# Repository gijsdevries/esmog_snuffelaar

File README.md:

# esmog_snuffelaar

## Software

## Hardware
### Orders
   - **Order #1** v1.0, 22-6-26, ce8a10

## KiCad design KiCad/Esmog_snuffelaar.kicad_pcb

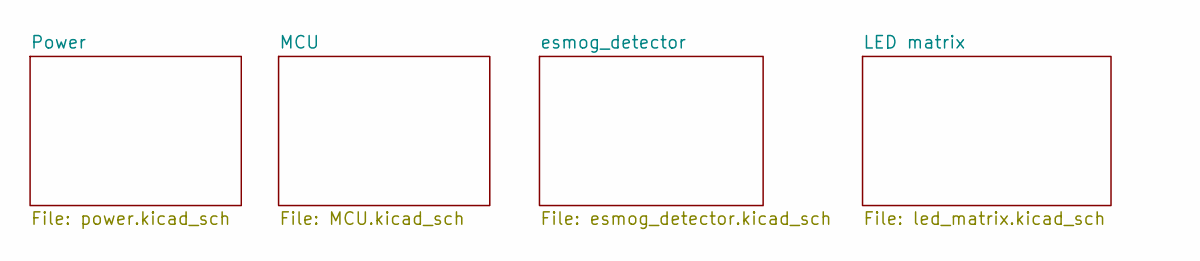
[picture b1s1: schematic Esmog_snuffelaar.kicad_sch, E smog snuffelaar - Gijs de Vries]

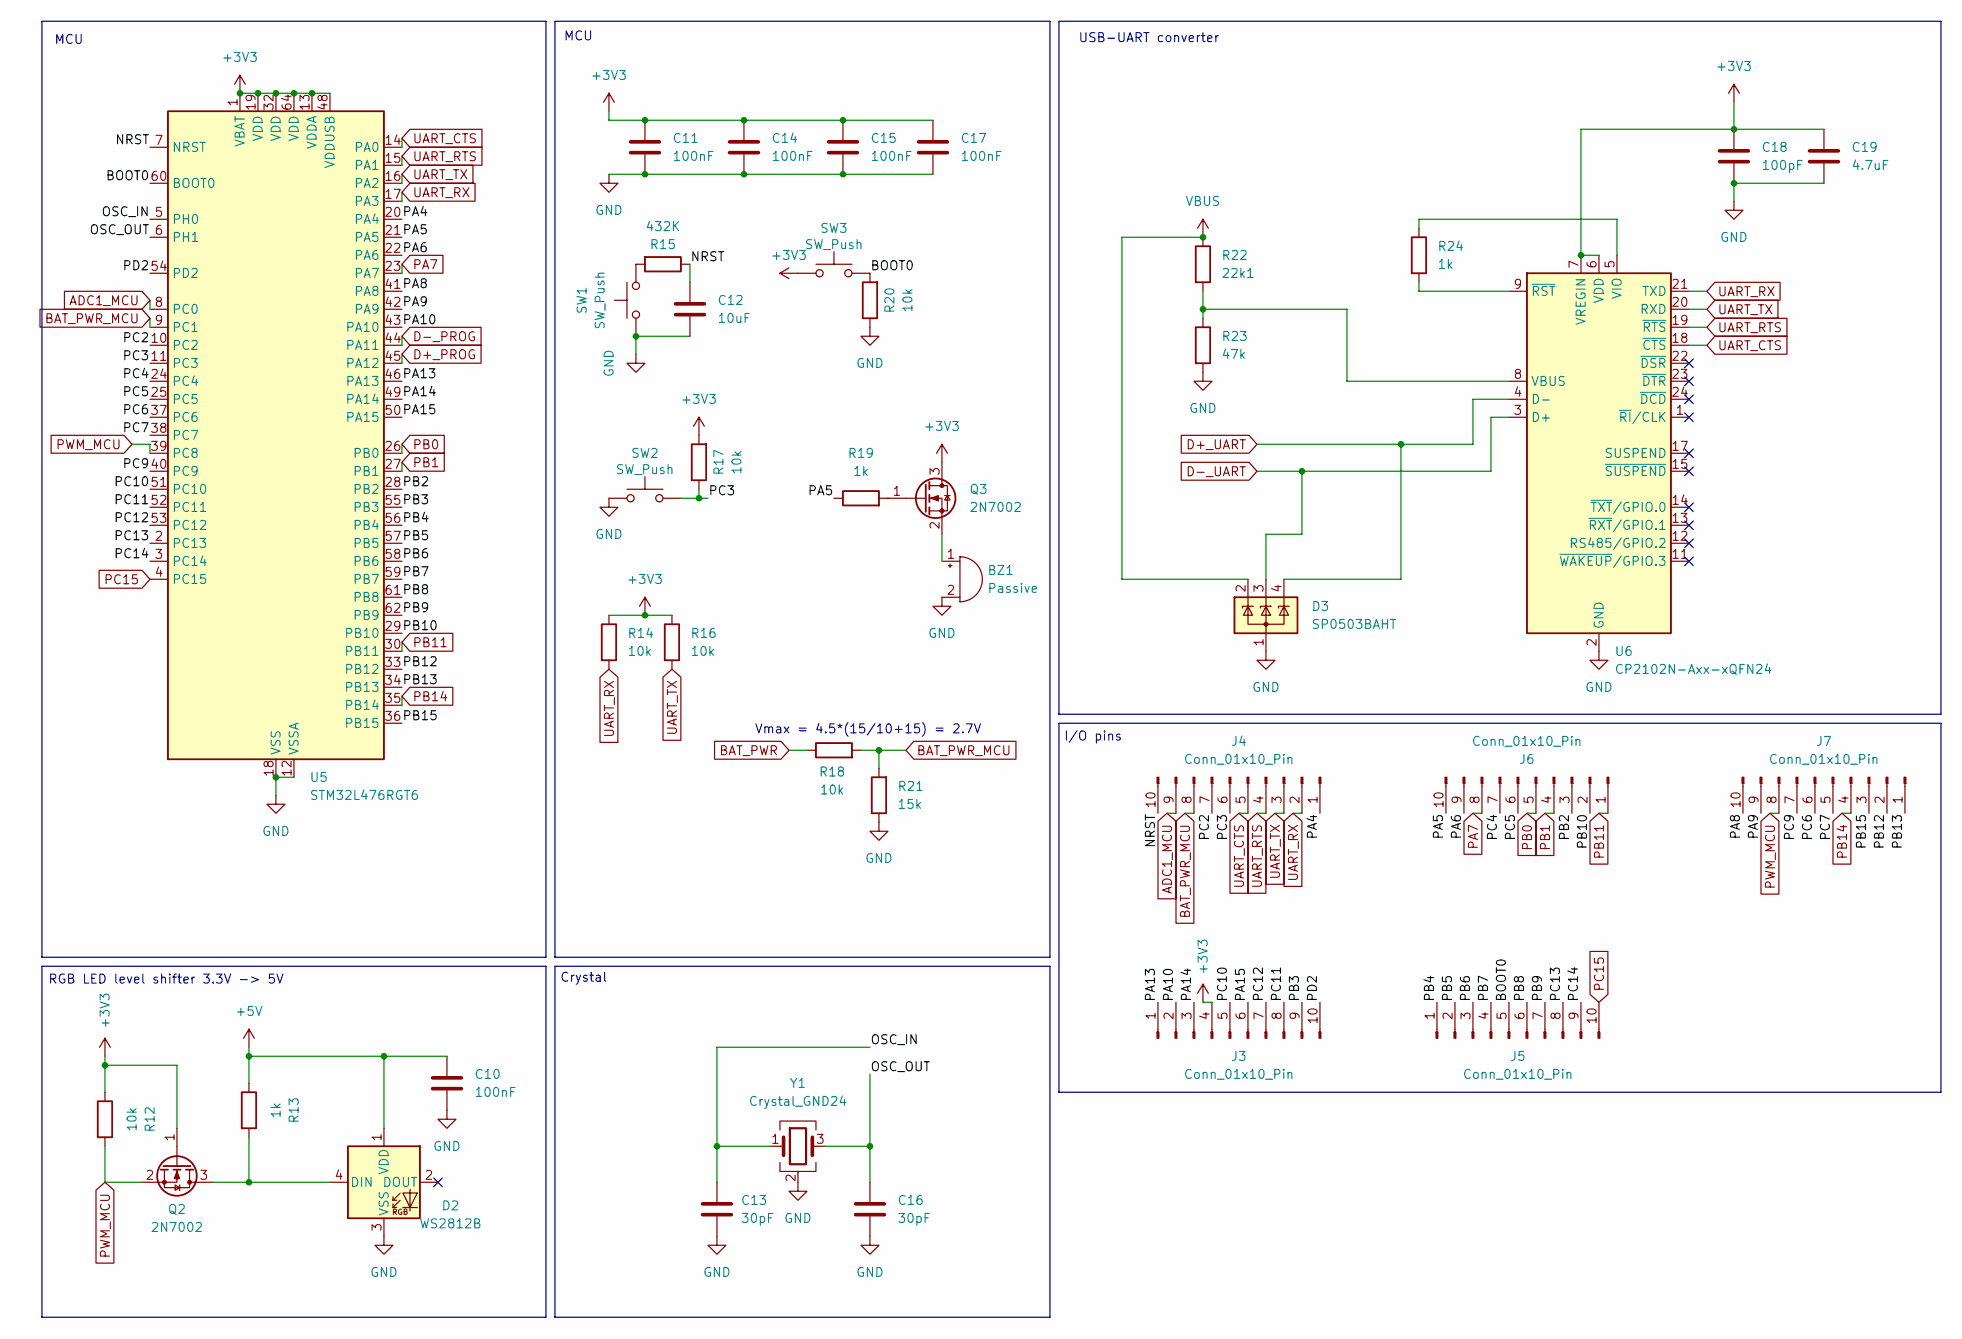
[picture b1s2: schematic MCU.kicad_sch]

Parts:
BZ1: Passive; Buzzer_TDK_PS1240P02BT_D12.2mm_H6.5mm; JLCPCB Part C76871
C10, C11, C14, C15, C17: 100nF; C_0603_1608Metric_Pad1.08x0.95mm_HandSolder; JLCPCB Part C1591
C12: 10uF; C_0603_1608Metric_Pad1.08x0.95mm_HandSolder; JLCPCB Part C1691
C13, C16: 30pF; C_0603_1608Metric_Pad1.08x0.95mm_HandSolder; JLCPCB Part C1658
C18: 100pF; C_0603_1608Metric_Pad1.08x0.95mm_HandSolder; JLCPCB Part C14858
C19: 4.7uF; C_0603_1608Metric_Pad1.08x0.95mm_HandSolder; JLCPCB Part C1705
D2: WS2812B; LED_WS2812B_PLCC4_5.0x5.0mm_P3.2mm; JLCPCB Part C527089
D3: SP0503BAHT; SOT-143; JLCPCB Part C7074
J3, J4, J5, J6, J7: Conn_01x10_Pin; PinHeader_2x05_P2.54mm_Vertical; JLCPCB Part C42431818
Q2, Q3: 2N7002; SOT-23; JLCPCB Part C916396
R12, R14, R16, R17, R18, R20: 10k; R_0603_1608Metric_Pad0.98x0.95mm_HandSolder; JLCPCB Part C2930027
R13, R19, R24: 1k; R_0603_1608Metric_Pad0.98x0.95mm_HandSolder; JLCPCB Part C2907002
R15: 432K; R_0603_1608Metric_Pad0.98x0.95mm_HandSolder; JLCPCB Part C234529
R21: 15k; R_0603_1608Metric_Pad0.98x0.95mm_HandSolder; JLCPCB Part C114682
R22: 22k1; R_0603_1608Metric_Pad0.98x0.95mm_HandSolder; JLCPCB Part C25961
R23: 47k; R_0603_1608Metric_Pad0.98x0.95mm_HandSolder; JLCPCB Part C2907042
SW1, SW2, SW3: SW_Push; SW_Push_SPST_NO_Alps_SKRK; JLCPCB Part C115357
U5: STM32L476RGT6; LQFP-64_10x10mm_P0.5mm; JLCPCB Part C74797
U6: CP2102N-Axx-xQFN24; QFN-24-1EP_4x4mm_P0.5mm_EP2.6x2.6mm; JLCPCB Part C964632
Y1: Crystal_GND24; Crystal_SMD_Abracon_ABM8AIG-4Pin_3.2x2.5mm; JLCPCB Part C9002

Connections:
+3V3: C11.2, C14.2, C15.2, C17.2, C18.1, C19.1, J3.4, Q2.1 (G), Q3.3 (D), R12.1, R14.1, R16.1, R17.2, SW3.1, U5.1 (VBAT), U5.13 (VDDA), U5.19 (VDD), U5.32 (VDD), U5.48 (VDDUSB), U5.64 (VDD), U6.6 (VDD), U6.7 (VREGIN); also elsewhere on the board
+5V: C10.2, D2.1 (VDD), R13.1; also elsewhere on the board
/MCU/BOOT0: J5.5, R20.2, SW3.2, U5.60 (BOOT0)
/MCU/NRST: C12.2, J4.10, R15.1, U5.7 (NRST)
/MCU/OSC_IN: C13.2, U5.5 (PH0), Y1.1
/MCU/OSC_OUT: C16.2, U5.6 (PH1), Y1.3
/MCU/PA4: J4.1, U5.20 (PA4)
/MCU/PA5: J6.10, R19.1, U5.21 (PA5)
/MCU/PA6: J6.9, U5.22 (PA6)
/MCU/PA8: J7.10, U5.41 (PA8)
/MCU/PA9: J7.9, U5.42 (PA9)
/MCU/PA10: J3.2, U5.43 (PA10)
/MCU/PA13: J3.1, U5.46 (PA13)
/MCU/PA14: J3.3, U5.49 (PA14)
/MCU/PA15: J3.6, U5.50 (PA15)
/MCU/PB2: J6.3, U5.28 (PB2)
/MCU/PB3: J3.9, U5.55 (PB3)
/MCU/PB4: J5.1, U5.56 (PB4)
/MCU/PB5: J5.2, U5.57 (PB5)
/MCU/PB6: J5.3, U5.58 (PB6)
/MCU/PB7: J5.4, U5.59 (PB7)
/MCU/PB8: J5.6, U5.61 (PB8)
/MCU/PB9: J5.7, U5.62 (PB9)
/MCU/PB10: J6.2, U5.29 (PB10)
/MCU/PB12: J7.2, U5.33 (PB12)
/MCU/PB13: J7.1, U5.34 (PB13)
/MCU/PB15: J7.3, U5.36 (PB15)
/MCU/PC2: J4.7, U5.10 (PC2)
/MCU/PC3: J4.6, R17.1, SW2.2, U5.11 (PC3)
/MCU/PC4: J6.7, U5.24 (PC4)
/MCU/PC5: J6.6, U5.25 (PC5)
/MCU/PC6: J7.6, U5.37 (PC6)
/MCU/PC7: J7.5, U5.38 (PC7)
/MCU/PC9: J7.7, U5.40 (PC9)
/MCU/PC10: J3.5, U5.51 (PC10)
/MCU/PC11: J3.8, U5.52 (PC11)
/MCU/PC12: J3.7, U5.53 (PC12)
/MCU/PC13: J5.8, U5.2 (PC13)
/MCU/PC14: J5.9, U5.3 (PC14)
/MCU/PD2: J3.10, U5.54 (PD2)
ADC1_MCU: J4.9, U5.8 (PC0); also elsewhere on the board
BAT_PWR: R18.1; also elsewhere on the board
BAT_PWR_MCU: J4.8, R18.2, R21.2, U5.9 (PC1)
D+_PROG: U5.45 (PA12); also elsewhere on the board
D+_UART: D3.4 (K), U6.4 (D-); also elsewhere on the board
D-_PROG: U5.44 (PA11); also elsewhere on the board
D-_UART: D3.3 (K), U6.3 (D+); also elsewhere on the board
GND: BZ1.2 (-), C10.1, C11.1, C12.1, C13.1, C14.1, C15.1, C16.1, C17.1, C18.2, C19.2, D2.3 (VSS), D3.1 (A), R20.1, R21.1, R23.2, SW1.1, SW2.1, U5.12 (VSSA), U5.18 (VSS), U5.31 (VSS), U5.47 (VSS), U5.63 (VSS), U6.2 (GND), U6.25 (GND), Y1.2 (G), Y1.4 (G); also elsewhere on the board
unnamed: BZ1.1 (+), Q3.2 (S)
unnamed: D2.4 (DIN), Q2.3 (D), R13.2
unnamed: Q3.1 (G), R19.2
unnamed: R15.2, SW1.2
unnamed: R22.2, R23.1, U6.8 (VBUS)
unnamed: R24.1, U6.5 (VIO)
unnamed: R24.2, U6.9 (~RST)
PA7: J6.8, U5.23 (PA7); also elsewhere on the board
PB0: J6.5, U5.26 (PB0); also elsewhere on the board
PB1: J6.4, U5.27 (PB1); also elsewhere on the board
PB11: J6.1, U5.30 (PB11); also elsewhere on the board
PB14: J7.4, U5.35 (PB14); also elsewhere on the board
PC15: J5.10, U5.4 (PC15)
PWM_MCU: J7.8, Q2.2 (S), R12.2, U5.39 (PC8)
UART_CTS: J4.5, U5.14 (PA0), U6.18 (~CTS)
UART_RTS: J4.4, U5.15 (PA1), U6.19 (~RTS)
UART_RX: J4.2, R14.2, U5.17 (PA3), U6.21 (TXD)
UART_TX: J4.3, R16.2, U5.16 (PA2), U6.20 (RXD)
VBUS: D3.2 (K), R22.1; also elsewhere on the board

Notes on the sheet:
MCU
I/O pins
Crystal
Vmax = 4.5*(15/10+15) = 2.7V
RGB LED level shifter 3.3V -> 5V
USB-UART converter

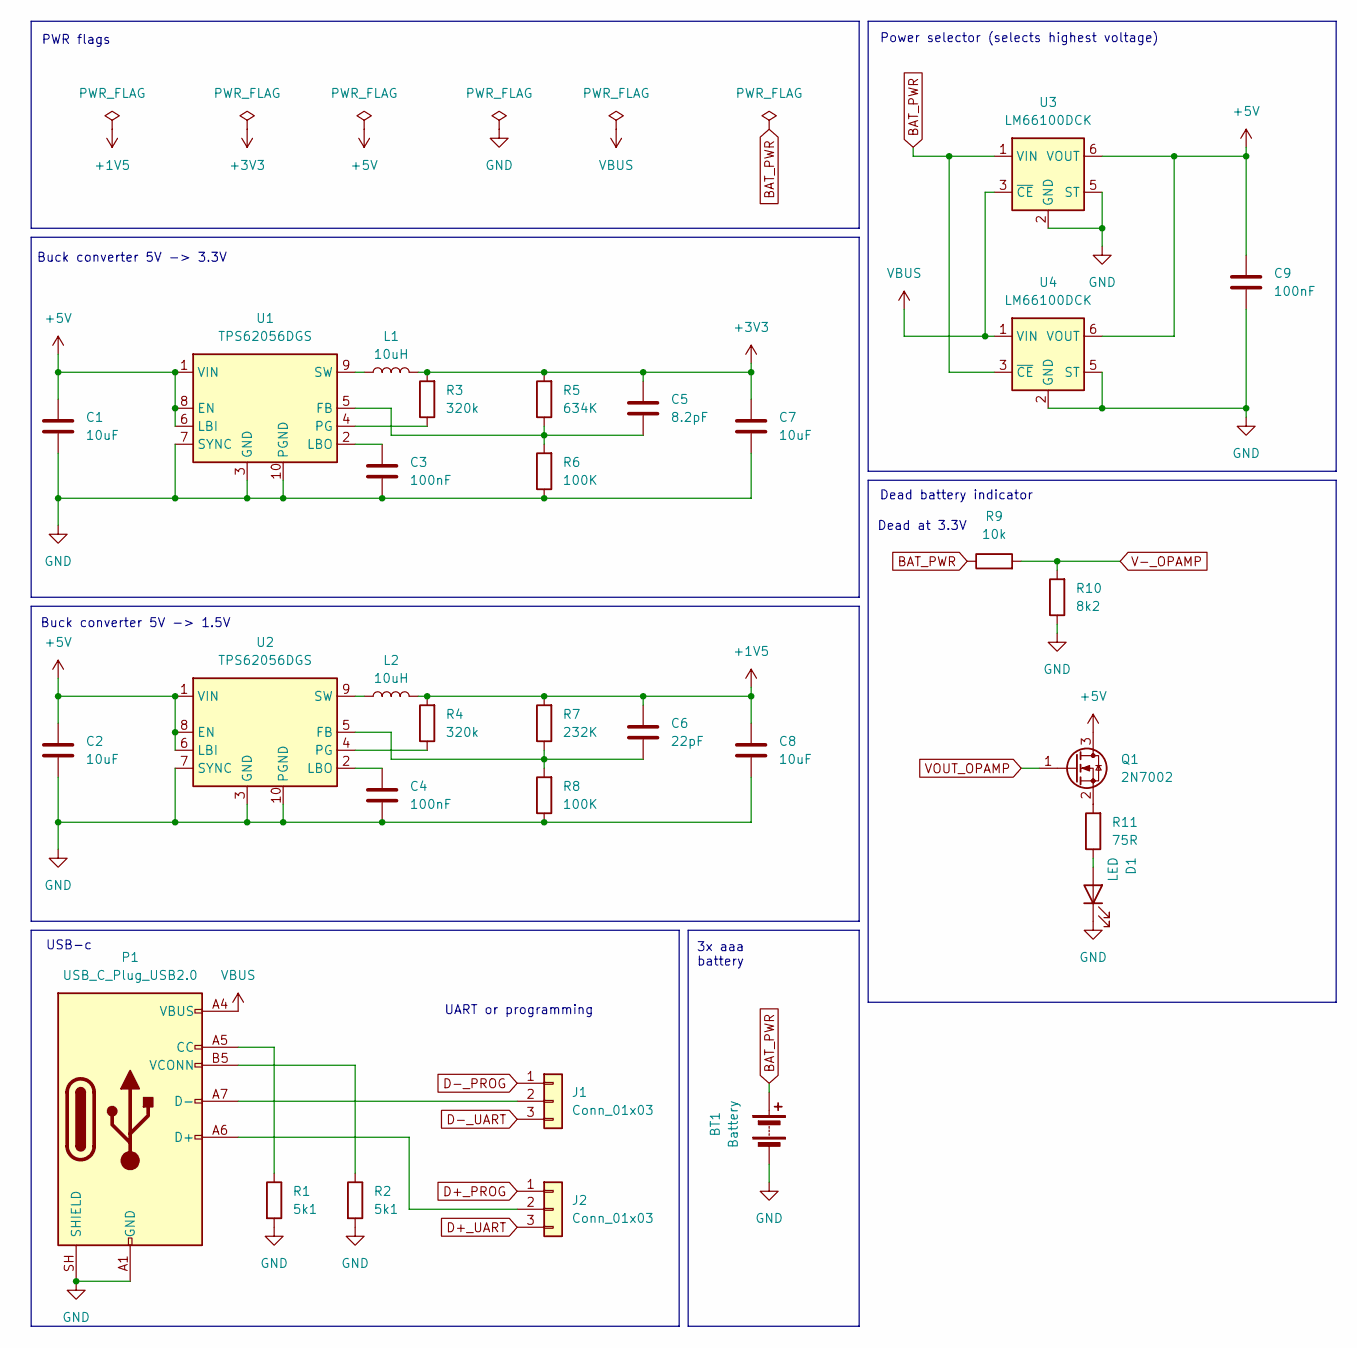
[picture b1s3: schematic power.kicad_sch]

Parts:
BT1: Battery; BatteryHolder_Keystone_2479_3xAAA; JLCPCB Part C5290193
C1, C2, C7, C8: 10uF; C_0603_1608Metric_Pad1.08x0.95mm_HandSolder; JLCPCB Part C1691
C3, C4, C9: 100nF; C_0603_1608Metric_Pad1.08x0.95mm_HandSolder; JLCPCB Part C1591
C5: 8.2pF; C_0603_1608Metric_Pad1.08x0.95mm_HandSolder; JLCPCB Part C1685
C6: 22pF; C_0603_1608Metric_Pad1.08x0.95mm_HandSolder; JLCPCB Part C1653
D1: LED; LED_0603_1608Metric; JLCPCB Part C2286
J1, J2: Conn_01x03; PinHeader_1x03_P2.54mm_Vertical
L1, L2: 10uH; L_APV_APH0420; JLCPCB Part C181721
P1: USB_C_Plug_USB2.0; USB_C_Receptacle_XKB_U262-16XN-4BVC11; JLCPCB Part C3025063
Q1: 2N7002; SOT-23; JLCPCB Part C916396
R1, R2: 5k1; R_0603_1608Metric_Pad0.98x0.95mm_HandSolder; JLCPCB Part C2907044
R3, R4: 320k; R_0603_1608Metric_Pad0.98x0.95mm_HandSolder; JLCPCB Part C862677
R5: 634K; R_0603_1608Metric_Pad0.98x0.95mm_HandSolder; JLCPCB Part C65831
R6, R8: 100K; R_0603_1608Metric_Pad0.98x0.95mm_HandSolder; JLCPCB Part C2906980
R7: 232K; R_0603_1608Metric_Pad0.98x0.95mm_HandSolder; JLCPCB Part C22913
R9: 10k; R_0603_1608Metric_Pad0.98x0.95mm_HandSolder; JLCPCB Part C2930027
R10: 8k2; R_0603_1608Metric_Pad0.98x0.95mm_HandSolder; JLCPCB Part C114637
R11: 75R; R_0603_1608Metric_Pad0.98x0.95mm_HandSolder; JLCPCB Part C112309
U1, U2: TPS62056DGS; TSSOP-10_3x3mm_P0.5mm; JLCPCB Part C7097
U3, U4: LM66100DCK; SOT-363_SC-70-6; JLCPCB Part C2832141

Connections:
+1V5: C6.2, C8.2, L2.2, R4.2, R7.2; also elsewhere on the board
+3V3: C5.2, C7.2, L1.2, R3.2, R5.2; also elsewhere on the board
+5V: C1.2, C2.2, C9.2, Q1.3 (D), U1.1 (VIN), U1.6 (LBI), U1.8 (EN), U2.1 (VIN), U2.6 (LBI), U2.8 (EN), U3.6 (VOUT), U4.6 (VOUT); also elsewhere on the board
BAT_PWR: BT1.1 (+), R9.1, U3.1 (VIN), U4.3 (~CE); also elsewhere on the board
D+_PROG: J2.1; also elsewhere on the board
D+_UART: J2.3; also elsewhere on the board
D-_PROG: J1.1; also elsewhere on the board
D-_UART: J1.3; also elsewhere on the board
GND: BT1.2 (-), C1.1, C2.1, C3.1, C4.1, C7.1, C8.1, C9.1, D1.1 (K), P1.A1 (GND), P1.A12 (GND), P1.B1 (GND), P1.B12 (GND), P1.SH (SHIELD), R1.2, R2.2, R6.1, R8.1, R10.1, U1.3 (GND), U1.7 (SYNC), U1.10 (PGND), U2.3 (GND), U2.7 (SYNC), U2.10 (PGND), U3.2 (GND), U3.5 (ST), U4.2 (GND), U4.5 (ST); also elsewhere on the board
unnamed: D1.2 (A), R11.1
unnamed: J1.2, P1.A7 (D-)
unnamed: J2.2, P1.A6 (D+)
unnamed: P1.A5 (CC), R1.1
unnamed: P1.B5 (VCONN), R2.1
unnamed: Q1.2 (S), R11.2
unnamed: C5.1, R5.1, R6.2, U1.5 (FB)
unnamed: C3.2, U1.2 (LBO)
unnamed: R3.1, U1.4 (PG)
unnamed: L1.1, U1.9 (SW)
unnamed: C6.1, R7.1, R8.2, U2.5 (FB)
unnamed: C4.2, U2.2 (LBO)
unnamed: R4.1, U2.4 (PG)
unnamed: L2.1, U2.9 (SW)
V-_OPAMP: R9.2, R10.2; also elsewhere on the board
VBUS: P1.A4 (VBUS), P1.A9 (VBUS), P1.B4 (VBUS), P1.B9 (VBUS), U3.3 (~CE), U4.1 (VIN); also elsewhere on the board
VOUT_OPAMP: Q1.1 (G); also elsewhere on the board

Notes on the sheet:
3x aaa battery
Buck converter 5V -> 3.3V
Dead at 3.3V
Power selector (selects highest voltage)
Buck converter 5V -> 1.5V
UART or programming
Dead battery indicator
PWR flags
USB-c

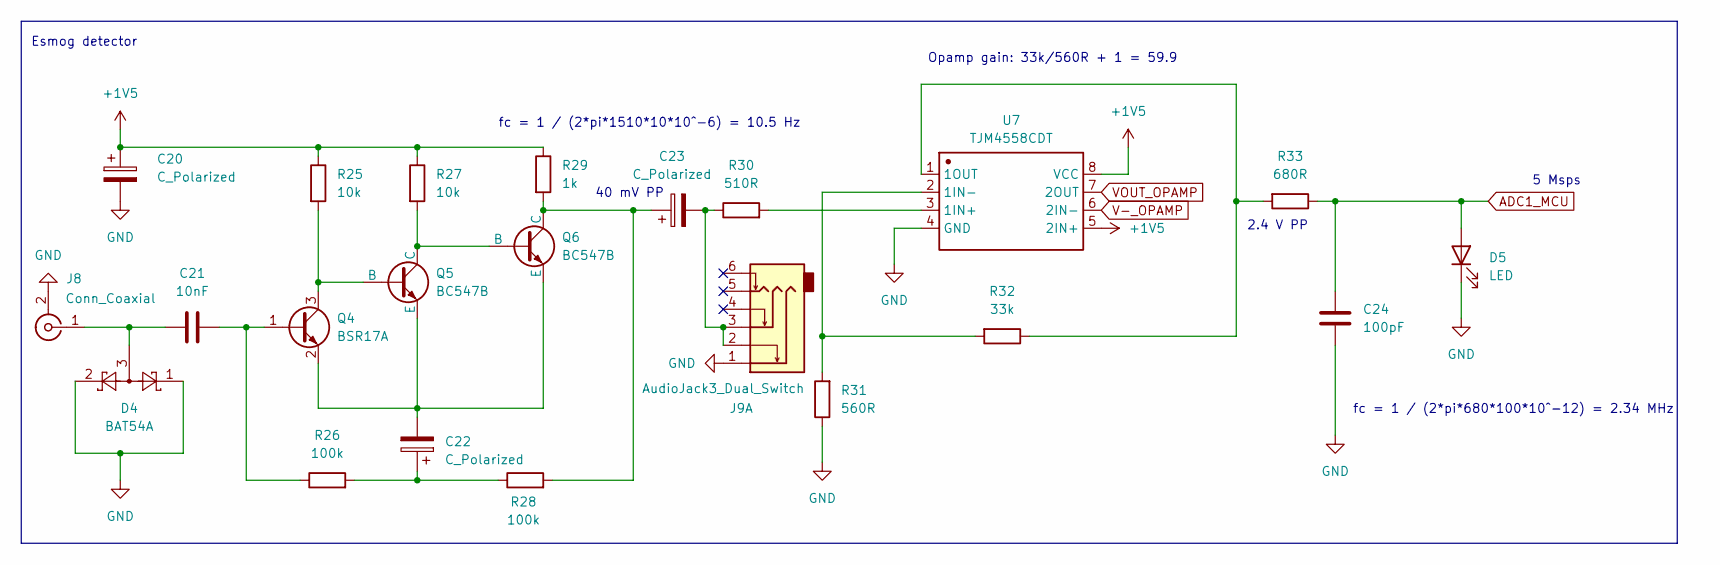
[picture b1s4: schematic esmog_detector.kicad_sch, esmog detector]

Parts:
C20, C22, C23: C_Polarized; CP_Elec_4x5.4; JLCPCB Part C213487
C21: 10nF; C_0603_1608Metric_Pad1.08x0.95mm_HandSolder; JLCPCB Part C1589
C24: 100pF; C_0603_1608Metric_Pad1.08x0.95mm_HandSolder; JLCPCB Part C14858
D4: BAT54A; SOT-23; JLCPCB Part C12743
D5: LED; LED_0603_1608Metric; JLCPCB Part C2286
J8: Conn_Coaxial; CONN-TH_AV-5; JLCPCB Part C18080
J9: AudioJack3_Dual_Switch; Audio_jack; JLCPCB Part C128987
Q4: BSR17A; SOT-23; JLCPCB Part C46682449
Q5, Q6: BC547B; TO-92; JLCPCB Part C713613
R25, R27: 10k; R_0603_1608Metric_Pad0.98x0.95mm_HandSolder; JLCPCB Part C2930027
R26, R28: 100k; R_0603_1608Metric_Pad0.98x0.95mm_HandSolder; JLCPCB Part C2906980
R29: 1k; R_0603_1608Metric_Pad0.98x0.95mm_HandSolder; JLCPCB Part C2907002
R30: 510R; R_0603_1608Metric_Pad0.98x0.95mm_HandSolder; JLCPCB Part C113299
R31: 560R; R_0603_1608Metric_Pad0.98x0.95mm_HandSolder; JLCPCB Part C23204
R32: 33k; R_0603_1608Metric_Pad0.98x0.95mm_HandSolder; JLCPCB Part C844778
R33: 680R; R_0603_1608Metric_Pad0.98x0.95mm_HandSolder; JLCPCB Part C23228
U7: TJM4558CDT; SOIC-8_5.3x5.3mm_P1.27mm; Manufacturer Part TJM4558CDT; JLCPCB Part C6955

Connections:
+1V5: C20.1, R25.1, R27.1, R29.1, U7.5 (2IN+), U7.8 (VCC); also elsewhere on the board
ADC1_MCU: C24.2, D5.2 (A), R33.1; also elsewhere on the board
GND: C20.2, C24.1, D4.1, D4.2, D5.1 (K), J8.2 (Ext), J9.1, R31.1, U7.4 (GND); also elsewhere on the board
unnamed: C22.1, R26.2, R28.1
unnamed: C23.2, J9.2, J9.3, R30.1
unnamed: C21.1, D4.3, J8.1 (In)
unnamed: C21.2, Q4.1 (B), R26.1
unnamed: Q4.3 (C), Q5.2 (B), R25.2
unnamed: C22.2, Q4.2 (E), Q5.3 (E), Q6.3 (E)
unnamed: Q5.1 (C), Q6.2 (B), R27.2
unnamed: C23.1, Q6.1 (C), R28.2, R29.2
unnamed: R30.2, U7.3 (1IN+)
unnamed: R31.2, R32.2, U7.2 (1IN-)
unnamed: R32.1, R33.2, U7.1 (1OUT)
V-_OPAMP: U7.6 (2IN-); also elsewhere on the board
VOUT_OPAMP: U7.7 (2OUT); also elsewhere on the board

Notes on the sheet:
5 Msps
fc = 1 / (2*pi*680*100*10^-12) = 2.34 MHz
40 mV PP
Esmog detector
fc = 1 / (2*pi*1510*10*10^-6) = 10.5 Hz
Opamp gain: 33k/560R + 1 = 59.9
2.4 V PP

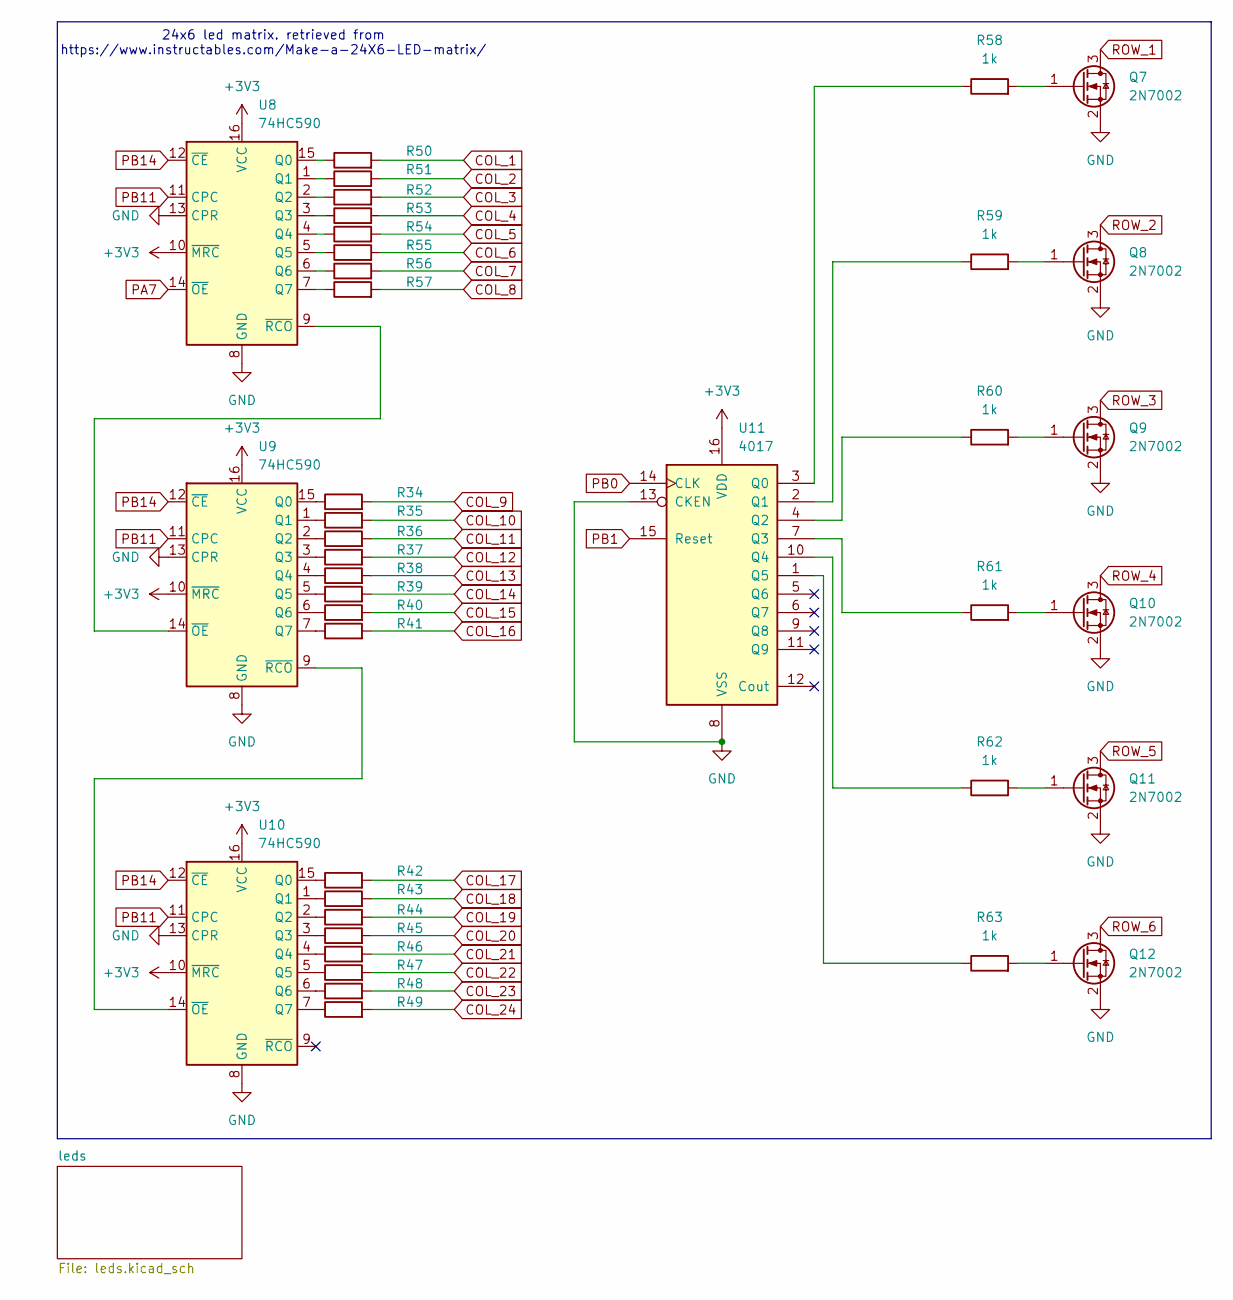
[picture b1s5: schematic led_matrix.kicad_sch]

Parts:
Q7, Q8, Q9, Q10, Q11, Q12: 2N7002; SOT-23; JLCPCB Part C916396
R34, R35, R36, R37, R38, R39, R40, R41, R42, R43, R44, R45, R46, R47, R48, R49, R50, R51, R52, R53, R54, R55, R56, R57: 75R; R_0603_1608Metric_Pad0.98x0.95mm_HandSolder; JLCPCB Part C112309
R58, R59, R60, R61, R62, R63: 1k; R_0603_1608Metric_Pad0.98x0.95mm_HandSolder; JLCPCB Part C2907002
U8, U9, U10: 74HC590; SOIC-16_3.9x9.9mm_P1.27mm; JLCPCB Part C5947
U11: 4017; SO-16_3.9x9.9mm_P1.27mm; JLCPCB Part C11349

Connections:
+3V3: U8.10 (~MRC), U8.16 (VCC), U9.10 (~MRC), U9.16 (VCC), U10.10 (~MRC), U10.16 (VCC), U11.16 (VDD); also elsewhere on the board
COL_1: R50.2; also elsewhere on the board
COL_2: R51.2; also elsewhere on the board
COL_3: R52.2; also elsewhere on the board
COL_4: R53.2; also elsewhere on the board
COL_5: R54.2; also elsewhere on the board
COL_6: R55.2; also elsewhere on the board
COL_7: R56.2; also elsewhere on the board
COL_8: R57.2; also elsewhere on the board
COL_9: R34.2; also elsewhere on the board
COL_10: R35.2; also elsewhere on the board
COL_11: R36.2; also elsewhere on the board
COL_12: R37.2; also elsewhere on the board
COL_13: R38.2; also elsewhere on the board
COL_14: R39.2; also elsewhere on the board
COL_15: R40.2; also elsewhere on the board
COL_16: R41.2; also elsewhere on the board
COL_17: R42.2; also elsewhere on the board
COL_18: R43.2; also elsewhere on the board
COL_19: R44.2; also elsewhere on the board
COL_20: R45.2; also elsewhere on the board
COL_21: R46.2; also elsewhere on the board
COL_22: R47.2; also elsewhere on the board
COL_23: R48.2; also elsewhere on the board
COL_24: R49.2; also elsewhere on the board
GND: Q7.2 (S), Q8.2 (S), Q9.2 (S), Q10.2 (S), Q11.2 (S), Q12.2 (S), U8.8 (GND), U8.13 (CPR), U9.8 (GND), U9.13 (CPR), U10.8 (GND), U10.13 (CPR), U11.8 (VSS), U11.13 (CKEN); also elsewhere on the board
unnamed: Q7.1 (G), R58.2
unnamed: Q8.1 (G), R59.2
unnamed: Q9.1 (G), R60.2
unnamed: Q10.1 (G), R61.2
unnamed: Q11.1 (G), R62.2
unnamed: Q12.1 (G), R63.2
unnamed: R50.1, U8.15 (Q0)
unnamed: R51.1, U8.1 (Q1)
unnamed: R52.1, U8.2 (Q2)
unnamed: R53.1, U8.3 (Q3)
unnamed: R54.1, U8.4 (Q4)
unnamed: R55.1, U8.5 (Q5)
unnamed: R56.1, U8.6 (Q6)
unnamed: R57.1, U8.7 (Q7)
unnamed: U8.9 (~RCO), U9.14 (~OE)
unnamed: R34.1, U9.15 (Q0)
unnamed: R35.1, U9.1 (Q1)
unnamed: R36.1, U9.2 (Q2)
unnamed: R37.1, U9.3 (Q3)
unnamed: R38.1, U9.4 (Q4)
unnamed: R39.1, U9.5 (Q5)
unnamed: R40.1, U9.6 (Q6)
unnamed: R41.1, U9.7 (Q7)
unnamed: R42.1, U10.15 (Q0)
unnamed: R43.1, U10.1 (Q1)
unnamed: R44.1, U10.2 (Q2)
unnamed: R45.1, U10.3 (Q3)
unnamed: R46.1, U10.4 (Q4)
unnamed: R47.1, U10.5 (Q5)
unnamed: R48.1, U10.6 (Q6)
unnamed: R49.1, U10.7 (Q7)
unnamed: U9.9 (~RCO), U10.14 (~OE)
unnamed: R58.1, U11.3 (Q0)
unnamed: R59.1, U11.2 (Q1)
unnamed: R60.1, U11.4 (Q2)
unnamed: R61.1, U11.7 (Q3)
unnamed: R62.1, U11.10 (Q4)
unnamed: R63.1, U11.1 (Q5)
PA7: U8.14 (~OE); also elsewhere on the board
PB0: U11.14 (CLK); also elsewhere on the board
PB1: U11.15 (Reset); also elsewhere on the board
PB11: U8.11 (CPC), U9.11 (CPC), U10.11 (CPC); also elsewhere on the board
PB14: U8.12 (~CE), U9.12 (~CE), U10.12 (~CE); also elsewhere on the board
ROW_1: Q7.3 (D); also elsewhere on the board
ROW_2: Q8.3 (D); also elsewhere on the board
ROW_3: Q9.3 (D); also elsewhere on the board
ROW_4: Q10.3 (D); also elsewhere on the board
ROW_5: Q11.3 (D); also elsewhere on the board
ROW_6: Q12.3 (D); also elsewhere on the board

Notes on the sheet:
24x6 led matrix. retrieved from https://www.instructables.com/Make-a-24X6-LED-matrix/

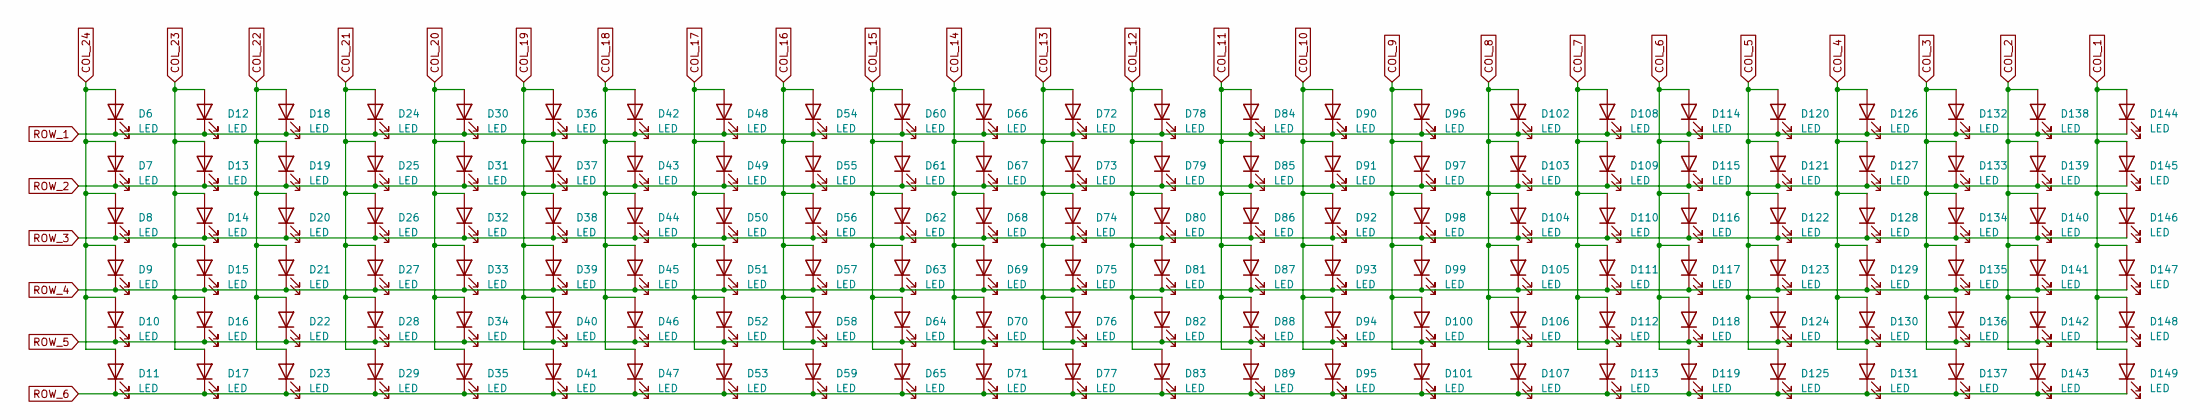
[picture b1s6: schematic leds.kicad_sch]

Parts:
D6, D7, D8, D9, D10, D11, D12, D13, D14, D15, D16, D17, D18, D19, D20, D21, D22, D23, D24, D25, D26, D27, D28, D29, D30, D31, D32, D33, D34, D35, D36, D37, D38, D39, D40, D41, D42, D43, D44, D45, D46, D47, D48, D49, D50, D51, D52, D53, D54, D55, D56, D57, D58, D59, D60, D61, D62, D63, D64, D65, D66, D67, D68, D69, D70, D71, D72, D73, D74, D75, D76, D77, D78, D79, D80, D81, D82, D83, D84, D85, D86, D87, D88, D89, D90, D91, D92, D93, D94, D95, D96, D97, D98, D99, D100, D101, D102, D103, D104, D105, D106, D107, D108, D109, D110, D111, D112, D113, D114, D115, D116, D117, D118, D119, D120, D121, D122, D123, D124, D125, D126, D127, D128, D129, D130, D131, D132, D133, D134, D135, D136, D137, D138, D139, D140, D141, D142, D143, D144, D145, D146, D147, D148, D149: LED; LED_0603_1608Metric; JLCPCB Part C2286

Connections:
COL_1: D144.2 (A), D145.2 (A), D146.2 (A), D147.2 (A), D148.2 (A), D149.2 (A); also elsewhere on the board
COL_2: D138.2 (A), D139.2 (A), D140.2 (A), D141.2 (A), D142.2 (A), D143.2 (A); also elsewhere on the board
COL_3: D132.2 (A), D133.2 (A), D134.2 (A), D135.2 (A), D136.2 (A), D137.2 (A); also elsewhere on the board
COL_4: D126.2 (A), D127.2 (A), D128.2 (A), D129.2 (A), D130.2 (A), D131.2 (A); also elsewhere on the board
COL_5: D120.2 (A), D121.2 (A), D122.2 (A), D123.2 (A), D124.2 (A), D125.2 (A); also elsewhere on the board
COL_6: D114.2 (A), D115.2 (A), D116.2 (A), D117.2 (A), D118.2 (A), D119.2 (A); also elsewhere on the board
COL_7: D108.2 (A), D109.2 (A), D110.2 (A), D111.2 (A), D112.2 (A), D113.2 (A); also elsewhere on the board
COL_8: D102.2 (A), D103.2 (A), D104.2 (A), D105.2 (A), D106.2 (A), D107.2 (A); also elsewhere on the board
COL_9: D96.2 (A), D97.2 (A), D98.2 (A), D99.2 (A), D100.2 (A), D101.2 (A); also elsewhere on the board
COL_10: D90.2 (A), D91.2 (A), D92.2 (A), D93.2 (A), D94.2 (A), D95.2 (A); also elsewhere on the board
COL_11: D84.2 (A), D85.2 (A), D86.2 (A), D87.2 (A), D88.2 (A), D89.2 (A); also elsewhere on the board
COL_12: D78.2 (A), D79.2 (A), D80.2 (A), D81.2 (A), D82.2 (A), D83.2 (A); also elsewhere on the board
COL_13: D72.2 (A), D73.2 (A), D74.2 (A), D75.2 (A), D76.2 (A), D77.2 (A); also elsewhere on the board
COL_14: D66.2 (A), D67.2 (A), D68.2 (A), D69.2 (A), D70.2 (A), D71.2 (A); also elsewhere on the board
COL_15: D60.2 (A), D61.2 (A), D62.2 (A), D63.2 (A), D64.2 (A), D65.2 (A); also elsewhere on the board
COL_16: D54.2 (A), D55.2 (A), D56.2 (A), D57.2 (A), D58.2 (A), D59.2 (A); also elsewhere on the board
COL_17: D48.2 (A), D49.2 (A), D50.2 (A), D51.2 (A), D52.2 (A), D53.2 (A); also elsewhere on the board
COL_18: D42.2 (A), D43.2 (A), D44.2 (A), D45.2 (A), D46.2 (A), D47.2 (A); also elsewhere on the board
COL_19: D36.2 (A), D37.2 (A), D38.2 (A), D39.2 (A), D40.2 (A), D41.2 (A); also elsewhere on the board
COL_20: D30.2 (A), D31.2 (A), D32.2 (A), D33.2 (A), D34.2 (A), D35.2 (A); also elsewhere on the board
COL_21: D24.2 (A), D25.2 (A), D26.2 (A), D27.2 (A), D28.2 (A), D29.2 (A); also elsewhere on the board
COL_22: D18.2 (A), D19.2 (A), D20.2 (A), D21.2 (A), D22.2 (A), D23.2 (A); also elsewhere on the board
COL_23: D12.2 (A), D13.2 (A), D14.2 (A), D15.2 (A), D16.2 (A), D17.2 (A); also elsewhere on the board
COL_24: D6.2 (A), D7.2 (A), D8.2 (A), D9.2 (A), D10.2 (A), D11.2 (A); also elsewhere on the board
ROW_1: D6.1 (K), D12.1 (K), D18.1 (K), D24.1 (K), D30.1 (K), D36.1 (K), D42.1 (K), D48.1 (K), D54.1 (K), D60.1 (K), D66.1 (K), D72.1 (K), D78.1 (K), D84.1 (K), D90.1 (K), D96.1 (K), D102.1 (K), D108.1 (K), D114.1 (K), D120.1 (K), D126.1 (K), D132.1 (K), D138.1 (K), D144.1 (K); also elsewhere on the board
ROW_2: D7.1 (K), D13.1 (K), D19.1 (K), D25.1 (K), D31.1 (K), D37.1 (K), D43.1 (K), D49.1 (K), D55.1 (K), D61.1 (K), D67.1 (K), D73.1 (K), D79.1 (K), D85.1 (K), D91.1 (K), D97.1 (K), D103.1 (K), D109.1 (K), D115.1 (K), D121.1 (K), D127.1 (K), D133.1 (K), D139.1 (K), D145.1 (K); also elsewhere on the board
ROW_3: D8.1 (K), D14.1 (K), D20.1 (K), D26.1 (K), D32.1 (K), D38.1 (K), D44.1 (K), D50.1 (K), D56.1 (K), D62.1 (K), D68.1 (K), D74.1 (K), D80.1 (K), D86.1 (K), D92.1 (K), D98.1 (K), D104.1 (K), D110.1 (K), D116.1 (K), D122.1 (K), D128.1 (K), D134.1 (K), D140.1 (K), D146.1 (K); also elsewhere on the board
ROW_4: D9.1 (K), D15.1 (K), D21.1 (K), D27.1 (K), D33.1 (K), D39.1 (K), D45.1 (K), D51.1 (K), D57.1 (K), D63.1 (K), D69.1 (K), D75.1 (K), D81.1 (K), D87.1 (K), D93.1 (K), D99.1 (K), D105.1 (K), D111.1 (K), D117.1 (K), D123.1 (K), D129.1 (K), D135.1 (K), D141.1 (K), D147.1 (K); also elsewhere on the board
ROW_5: D10.1 (K), D16.1 (K), D22.1 (K), D28.1 (K), D34.1 (K), D40.1 (K), D46.1 (K), D52.1 (K), D58.1 (K), D64.1 (K), D70.1 (K), D76.1 (K), D82.1 (K), D88.1 (K), D94.1 (K), D100.1 (K), D106.1 (K), D112.1 (K), D118.1 (K), D124.1 (K), D130.1 (K), D136.1 (K), D142.1 (K), D148.1 (K); also elsewhere on the board
ROW_6: D11.1 (K), D17.1 (K), D23.1 (K), D29.1 (K), D35.1 (K), D41.1 (K), D47.1 (K), D53.1 (K), D59.1 (K), D65.1 (K), D71.1 (K), D77.1 (K), D83.1 (K), D89.1 (K), D95.1 (K), D101.1 (K), D107.1 (K), D113.1 (K), D119.1 (K), D125.1 (K), D131.1 (K), D137.1 (K), D143.1 (K), D149.1 (K); also elsewhere on the board

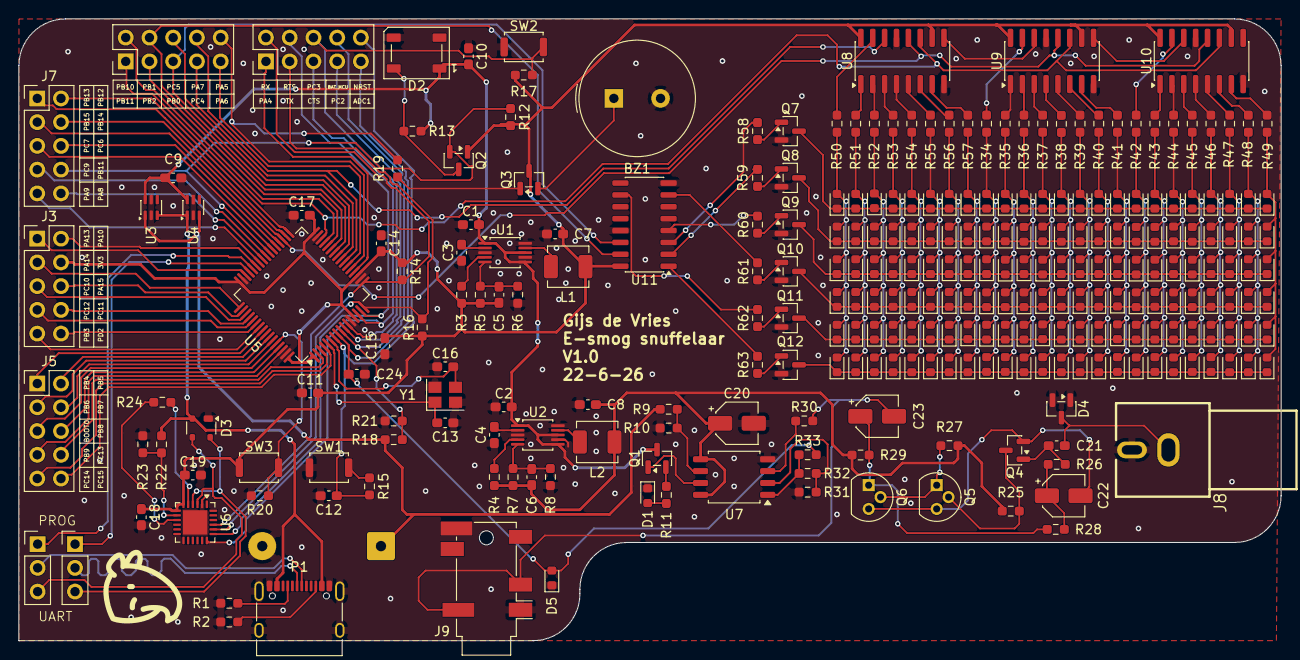
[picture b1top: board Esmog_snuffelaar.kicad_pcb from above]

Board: 2 copper layers, 135.0 x 66.5 mm, 277 parts (1 on the bottom side), 163 nets.

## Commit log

2026-06-19 added kicad project
2026-06-20 changed components and excluded from BOM
2026-06-20 changed more part#
2026-06-21 d+ and d- length matching
2026-06-22 changed some out of stock parts
2026-06-22 changed readme
2026-06-22 cleanup readme
2026-06-22 deleted one space bruh
